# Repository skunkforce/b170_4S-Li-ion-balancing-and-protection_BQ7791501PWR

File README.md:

# edgy_board number b170
This design is part of the [edgy board project](https://github.com/skunkforce/edgy_boards).

# getting started
This repository uses submodules. After cloning use the command 

```$ git submodule update --init --recursive```

to pull the submodules before opening the project with kicad. 

# Tests
Tests can be found in [TESTS.md](TESTS.md)

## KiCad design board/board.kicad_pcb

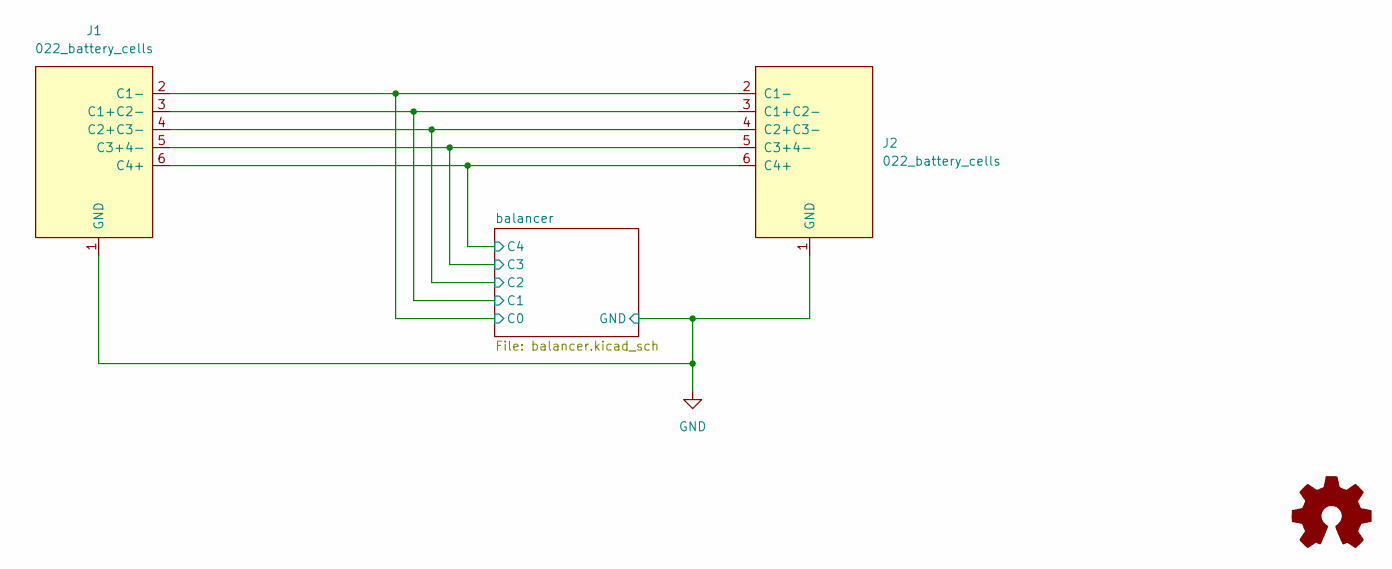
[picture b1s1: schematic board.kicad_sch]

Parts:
J1: 022_battery_cells; on_edge_2x05_device
J2: 022_battery_cells; on_edge_2x05_host
LOGO1: Logo_Open_Hardware_Small; OSHW-Symbol_6.7x6mm_SilkScreen

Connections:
/balancer/C0: J1.2 (C1-), J2.2 (C1-); also elsewhere on the board
/balancer/C1: J1.3 (C1+C2-), J2.3 (C1+C2-); also elsewhere on the board
/balancer/C2: J1.4 (C2+C3-), J2.4 (C2+C3-); also elsewhere on the board
/balancer/C3: J1.5 (C3+4-), J2.5 (C3+4-); also elsewhere on the board
/balancer/C4: J1.6 (C4+), J2.6 (C4+); also elsewhere on the board
GND: J1.1 (GND), J2.1 (GND); also elsewhere on the board

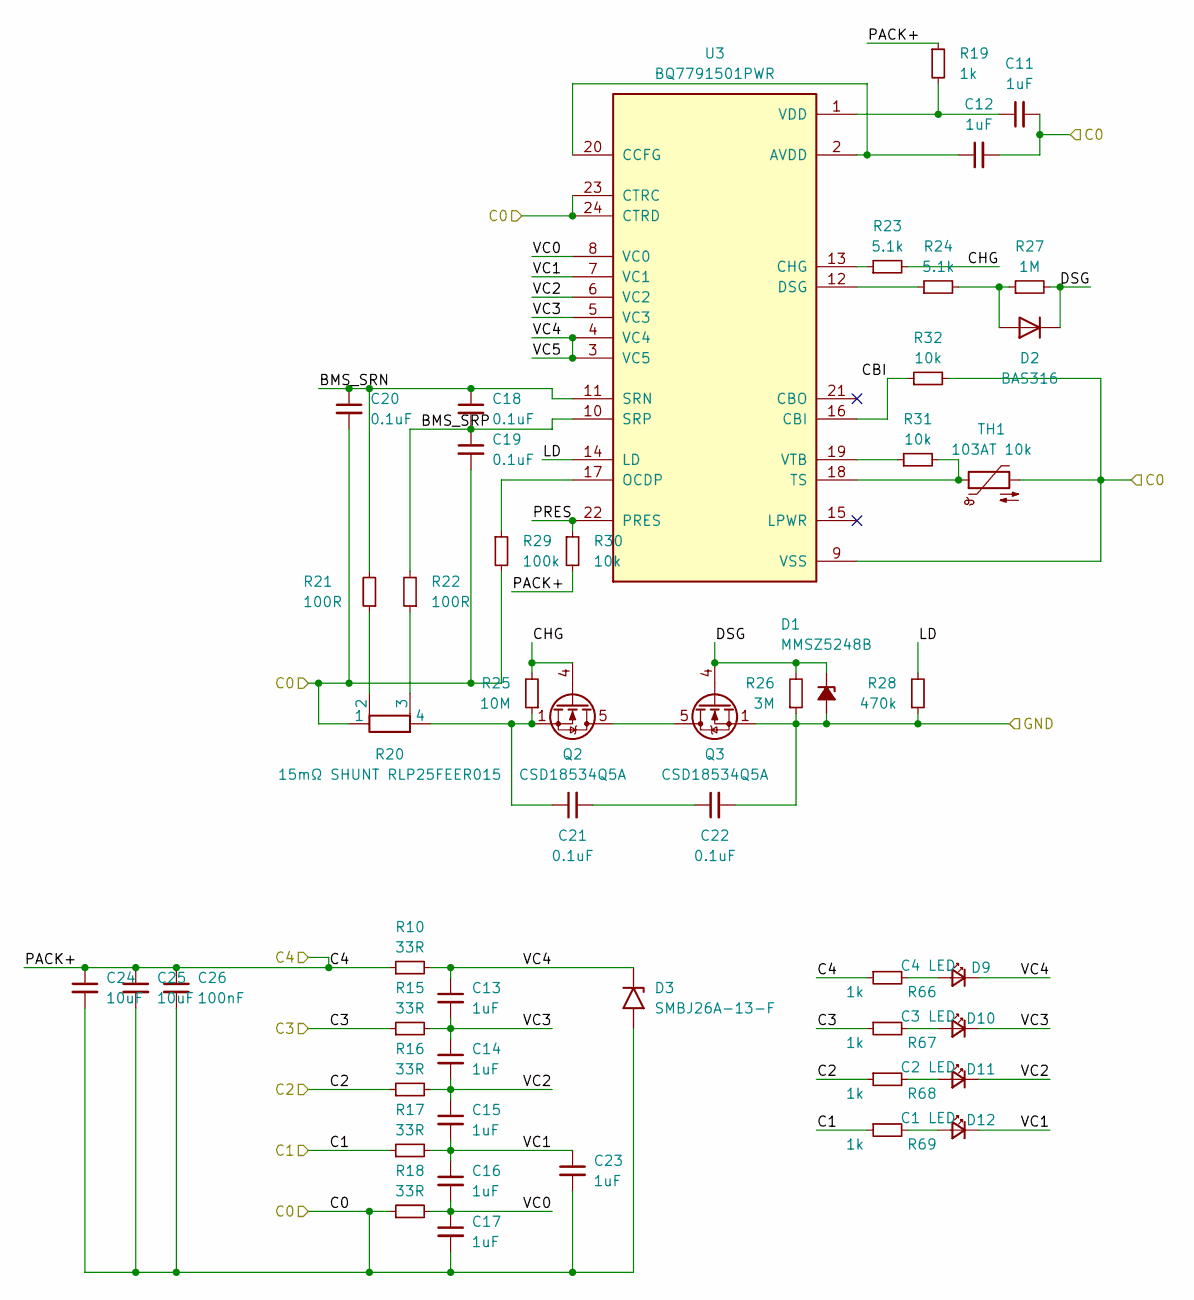
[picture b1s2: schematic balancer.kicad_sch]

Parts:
C11, C12, C13, C14, C15, C16, C17, C23: 1uF; C_0603_1608Metric; LCSC C15849
C18, C19, C20, C21, C22: 0.1uF; C_0603_1608Metric; LCSC C14663
C24, C25: 10uF; C_0603_1608Metric; LCSC C96446
C26: 100nF; C_0603_1608Metric; LCSC C14663
D1: MMSZ5248B; D_SOD-123; LCSC C82088
D2: BAS316; D_SOD-323; LCSC C109218
D3: SMBJ26A-13-F; D_SMB; LCSC C135062
D9: C4 LED; LED_0603_1608Metric; LCSC C2286
D10: C3 LED; LED_0603_1608Metric; LCSC C2286
D11: C2 LED; LED_0603_1608Metric; LCSC C2286
D12: C1 LED; LED_0603_1608Metric; LCSC C2286
Q2, Q3: CSD18534Q5A; TDSON-8-1; LCSC C115943
R10, R15, R16, R17, R18: 33R; R_0603_1608Metric; LCSC C23140
R19, R66, R67, R68, R69: 1k; R_0603_1608Metric; LCSC C21190
R20: 15mΩ SHUNT RLP25FEER015; R_Shunt_Vishay_WSK2512_6332Metric_T1.19mm; LCSC C393085
R21, R22: 100R; R_0603_1608Metric; LCSC C22775
R23, R24: 5.1k; R_0603_1608Metric; LCSC C23186
R25: 10M; R_0603_1608Metric; LCSC C7250
R26: 3M; R_0603_1608Metric; LCSC C23156
R27: 1M; R_0603_1608Metric; LCSC C22935
R28: 470k; R_0603_1608Metric; LCSC C23178
R29: 100k; R_0603_1608Metric; LCSC C25803
R30, R31, R32: 10k; R_0603_1608Metric; LCSC C25804
TH1: 103AT 10k; PinHeader_1x02_P2.54mm_Vertical
U3: BQ7791501PWR; TSSOP-24_4.4x7.8mm_P0.65mm; PARTREV H; LCSC C2876946

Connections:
/balancer/BMS_SRN: C18.1, C20.1, R21.2, U3.11 (SRN)
/balancer/BMS_SRP: C18.2, C19.1, R22.2, U3.10 (SRP)
/balancer/C0: C11.2, C12.2, C17.2, C19.2, C20.2, C23.2, C24.2, C25.2, C26.2, D3.2 (A2), R18.1, R20.1, R29.2, R32.2, TH1.2, U3.9 (VSS), U3.23 (CTRC), U3.24 (CTRD); also elsewhere on the board
/balancer/C1: R17.1, R69.1; also elsewhere on the board
/balancer/C2: R16.1, R68.1; also elsewhere on the board
/balancer/C3: R15.1, R67.1; also elsewhere on the board
/balancer/C4: C24.1, C25.1, C26.1, R10.1, R19.1, R30.2, R66.1; also elsewhere on the board
/balancer/CBI: R32.1, U3.16 (CBI)
/balancer/CHG: Q2.4 (G), R23.2, R25.2
/balancer/DSG: D1.1 (K), D2.1 (K), Q3.4 (G), R26.2, R27.2
/balancer/LD: R28.2, U3.14 (LD)
/balancer/PRES: R30.1, U3.22 (PRES)
/balancer/VC0: C16.2, C17.1, R18.2, U3.8 (VC0)
/balancer/VC1: C15.2, C16.1, C23.1, D12.1 (K), R17.2, U3.7 (VC1)
/balancer/VC2: C14.2, C15.1, D11.1 (K), R16.2, U3.6 (VC2)
/balancer/VC3: C13.2, C14.1, D10.1 (K), R15.2, U3.5 (VC3)
/balancer/VC4: C13.1, D3.1 (A1), D9.1 (K), R10.2, U3.3 (VC5), U3.4 (VC4)
GND: C22.2, D1.2 (A), Q3.1 (S), Q3.2 (S), Q3.3 (S), R26.1, R28.1; also elsewhere on the board
unnamed: C21.1, Q2.1 (S), Q2.2 (S), Q2.3 (S), R20.4, R25.1
unnamed: C21.2, C22.1
unnamed: D2.2 (A), R24.2, R27.1
unnamed: D9.2 (A), R66.2
unnamed: D10.2 (A), R67.2
unnamed: D11.2 (A), R68.2
unnamed: D12.2 (A), R69.2
unnamed: Q2.5 (D), Q3.5 (D)
unnamed: R20.2, R21.1
unnamed: R20.3, R22.1
unnamed: C12.1, U3.2 (AVDD), U3.20 (CCFG)
unnamed: R23.1, U3.13 (CHG)
unnamed: R24.1, U3.12 (DSG)
unnamed: R29.1, U3.17 (OCDP)
unnamed: R31.2, TH1.1, U3.18 (TS)
unnamed: C11.1, R19.2, U3.1 (VDD)
unnamed: R31.1, U3.19 (VTB)

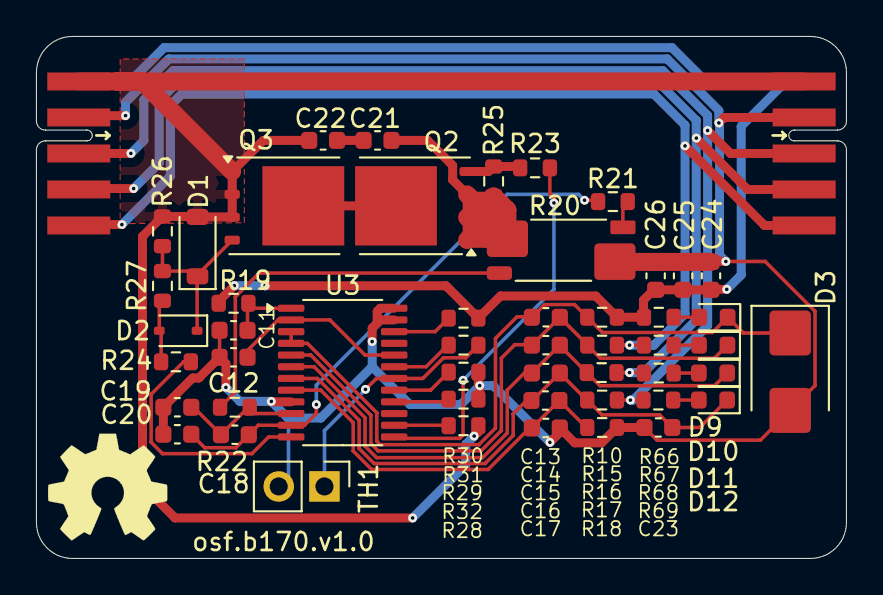
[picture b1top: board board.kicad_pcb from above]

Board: 2 copper layers, 45.0 x 29.0 mm, 53 parts (0 on the bottom side), 35 nets.

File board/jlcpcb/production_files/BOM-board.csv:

Comment,Designator,Footprint,LCSC,Quantity
BAS316,D2,D_SOD-323,C109218,1
CSD18534Q5A,"Q2,Q3",TDSON-8-1,C115943,2
SMBJ26A-13-F,D3,D_SMB,C135062,1
0.1uF,"C18,C19,C20,C21,C22,C26",C_0603_1608Metric,C14663,6
1uF,"C11,C12,C13,C14,C15,C16,C17,C23",C_0603_1608Metric,C15849,8
1k,"R19,R66,R67,R68,R69",R_0603_1608Metric,C21190,5
100R,"R21,R22",R_0603_1608Metric,C22775,2
C3 LED,"D10,D11,D12,D9",LED_0603_1608Metric,C2286,4
1M,R27,R_0603_1608Metric,C22935,1
33R,"R10,R15,R16,R17,R18",R_0603_1608Metric,C23140,5
3M,R26,R_0603_1608Metric,C23156,1
470k,R28,R_0603_1608Metric,C23178,1
5.1k,"R23,R24",R_0603_1608Metric,C23186,2
100k,R29,R_0603_1608Metric,C25803,1
10k,"R30,R31,R32",R_0603_1608Metric,C25804,3
BQ7791501PWR,U3,TSSOP-24_4.4x7.8mm_P0.65mm,C2876946,1
15mΩ SHUNT RLP25FEER015,R20,R_Shunt_Vishay_WSK2512_6332Metric_T1.19mm,C393085,1
10M,R25,R_0603_1608Metric,C7250,1
MMSZ5248B,D1,D_SOD-123,C82088,1
10uF,"C24,C25",C_0603_1608Metric,C96446,2
022_battery_cells,J2,on_edge_2x05_host,,1
022_battery_cells,J1,on_edge_2x05_device,,1
Logo_Open_Hardware_Small,LOGO1,OSHW-Symbol_6.7x6mm_SilkScreen,,1
103AT 10k,TH1,PinHeader_1x02_P2.54mm_Vertical,,1

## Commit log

2025-05-12 initial
2025-05-12 added production files
2025-11-25 added board number on silk screen
